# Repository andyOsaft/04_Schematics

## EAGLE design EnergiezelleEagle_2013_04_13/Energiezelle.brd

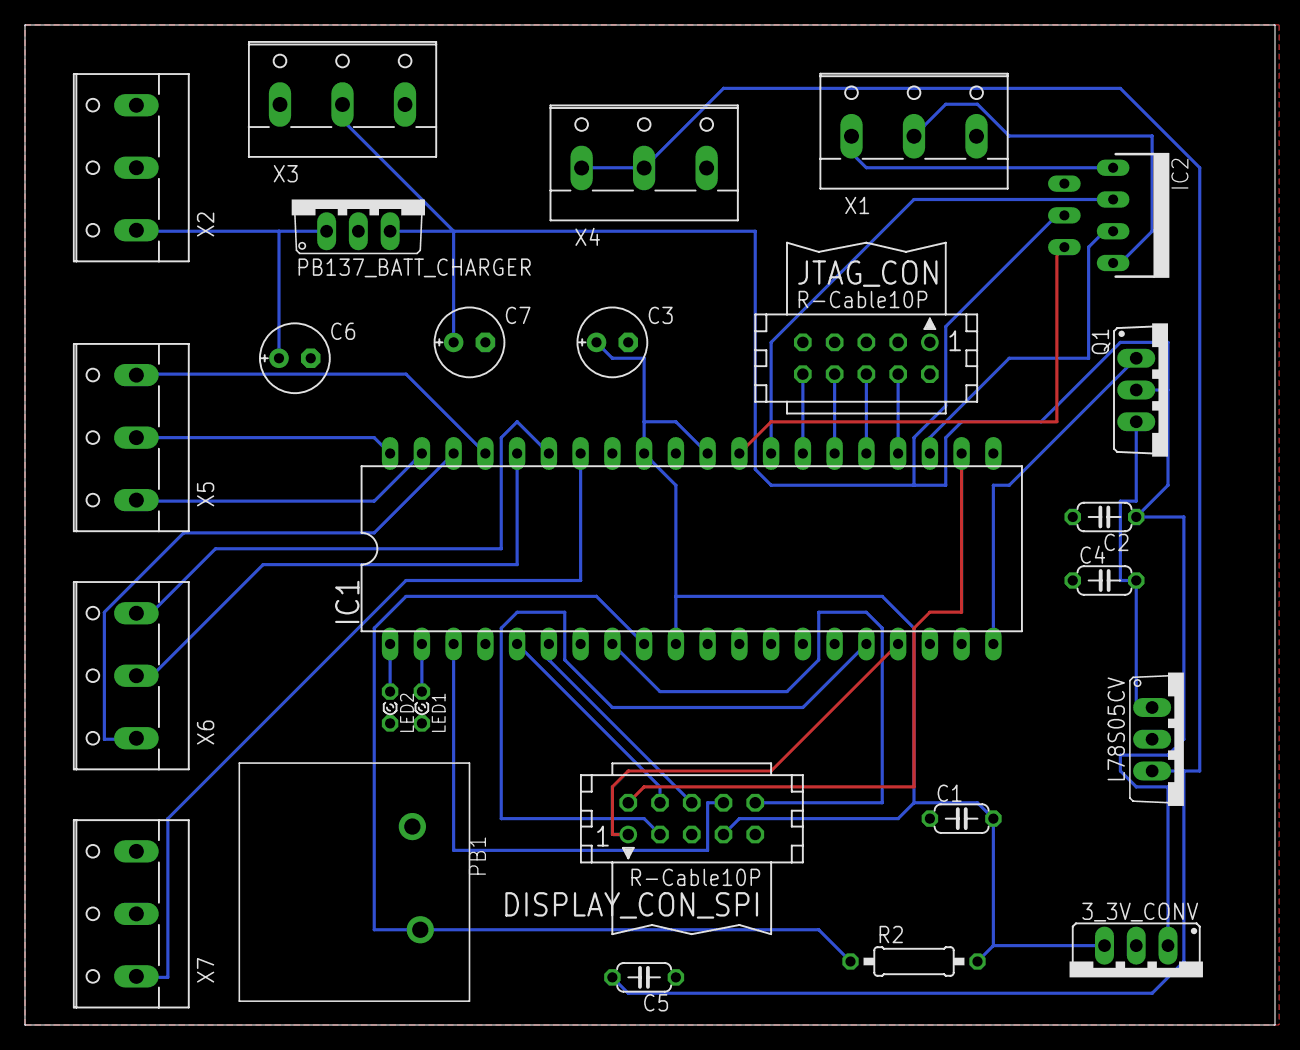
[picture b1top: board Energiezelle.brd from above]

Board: 2 copper layers, 100.0 x 80.0 mm, 26 parts (0 on the bottom side), 33 nets.

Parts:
3_3V_CONV: 3.3VRegulator; TO220S
C1, C2, C5: 100n; C050-024X044
C3, C7: 10u; E2,5-6E
C4: 330n; C050-024X044
C6: 1u; E2,5-6E
DISPLAY_CON_SPI: CON10L
IC1: MEGA32-P; DIL40
IC2: BTS621; P-TO220-7-11
JTAG_CON: CON10L
L78S05CV: 788TV; TO220V
LED1: green; LSU260
LED2: red; LSU260
PB1: PBNO-M
PB137_BATT_CHARGER: 788TV; TO220V
Q1: IRLU8721; TO220BV
R2: 10k; 0207/10
X1, X2, X3, X4, X5, X6, X7: W237-103

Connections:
+3V3: 3_3V_CONV.3, C1.2, C3.+, DISPLAY_CON_SPI.7, IC1.10, IC1.30, IC1.32, R2.2
+5V: C5.2, L78S05CV.3, X4.1, X4.2
+12V: 3_3V_CONV.1, C2.1, C7.+, IC2.4, PB137_BATT_CHARGER.3, Q1.D, X3.2
BUTTON_LEFT: DISPLAY_CON_SPI.1, IC1.17
BUTTON_RIGHT: DISPLAY_CON_SPI.3, IC1.16
GND: 3_3V_CONV.2, C1.1, C2.2, C3.-, C4.1, C5.1, C6.-, C7.-, DISPLAY_CON_SPI.9, IC1.11, IC1.31, IC2.2, L78S05CV.2, LED1.K, LED2.K, PB1.P$1, PB137_BATT_CHARGER.2, X1.3, X2.2, X3.3, X4.3
unnamed: IC1.28, IC2.3
unnamed: IC1.29, IC2.6
unnamed: IC1.23, IC2.5
unnamed: IC1.9, PB1.P$2, R2.1
unnamed: DISPLAY_CON_SPI.10, IC1.8
unnamed: DISPLAY_CON_SPI.8, IC1.3
unnamed: DISPLAY_CON_SPI.6, IC1.6
unnamed: DISPLAY_CON_SPI.4, IC1.5
unnamed: IC2.1, X1.1
unnamed: IC2.7, X1.2
unnamed: C6.+, PB137_BATT_CHARGER.1, X2.1
unnamed: IC1.27, JTAG_CON.10
unnamed: IC1.26, JTAG_CON.8
unnamed: IC1.25, JTAG_CON.6
unnamed: IC1.24, JTAG_CON.4
unnamed: IC1.39, X5.1
unnamed: IC1.40, X5.2
unnamed: IC1.37, X5.3
unnamed: IC1.38, X6.1
unnamed: IC1.36, X6.2
unnamed: IC1.35, X6.3
unnamed: IC1.34, X7.1
unnamed: IC1.1, LED2.A
unnamed: IC1.2, LED1.A
unnamed: C4.2, L78S05CV.1, Q1.S
unnamed: IC1.20, Q1.G
RESET: DISPLAY_CON_SPI.2, IC1.22

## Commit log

2014-07-06 Initial repo commit
    Added all schematic files
